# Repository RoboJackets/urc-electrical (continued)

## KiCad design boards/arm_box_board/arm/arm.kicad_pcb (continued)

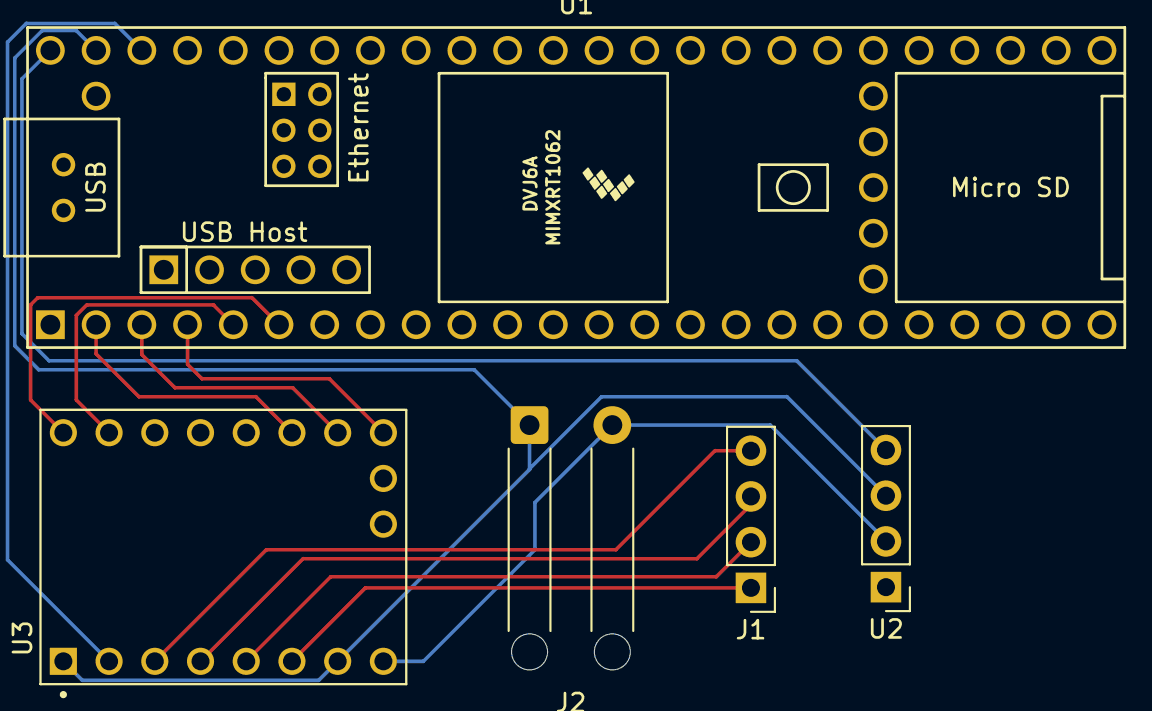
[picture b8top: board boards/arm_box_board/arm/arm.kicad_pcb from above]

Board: 2 copper layers, 5 parts (0 on the bottom side), 13 nets.

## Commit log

2024-03-07 Added BMS balance leads.
2024-04-11 Added Status Light Board
    To be merged into Main Board eventually
2024-04-11 arm_box_board
2024-04-13 Preliminary progress on science board.
2024-04-14 Finished preliminary routing. Used through-hole footprints.
2024-04-14 Updated board measurements.
2024-04-17 README.tex
2024-04-17 Rename README.tex to README.text
2024-04-17 Updated main schematic
2024-04-22 Updated Main PCB
2024-04-24 Added Ethernet module.
2024-04-24 Updated Arm board with ethernet
    updated on 04/24
2024-04-24 Added Logo
2024-04-24 Switched RX/TX pin position and IMU pin position
2024-04-25 moved science board to boards
2024-04-25 cap added
2024-04-25 Added logo to science board
2024-04-26 Added Holes to Main PCB
2024-04-28 Corrected Ethernet pin matches to teensy
2024-04-28 updated GND plane and unconnected pins
2024-04-28 updated science board-GND
2024-04-28 updated main board
2024-04-28 labelled digital input pins
2024-04-28 Extra pins/labels added
2024-04-28 last update
2024-05-02 Changes to Science and Arm Board
    Added pin labels to both boards
    Fixed Mislabeled Stepper Board Footprint in Arm board
    Added extra digital pins and ground in Science Board
2024-05-04 Removed I2C level converter from Science Board
    BRUH
    The temperature probe works running on 3.3V so the level converter for I2C wasn't even necessary on the Science Board. I have removed it from the schematic and updated the PCB layout.
2024-05-05 Prepared Boards for PCB Manufacture
    Added GND line for IMU on Main Board
    Fixed Silkscreen Text Size for PCB Manufacture on Science, Main, and Arm boards
    Generated Gerber Files for Science, Main, and Arm boards
2024-05-10 Changed Resistor Value for status light circuit in Main Board
    Updated value to 1k from 100 Ohms
2024-08-28 Solo Uno Module Side Panel PCB
    started
2024-09-15 Made Symbols and Footprint Library for RoboNav
2024-09-22 Add files via upload
    Updated Solo uno board
2024-10-14 Started 4 layer PCB
2024-11-03 4 layer main
2024-11-03 updated 4-layer
2024-11-03 4layer update
2024-11-04 Updated Solon
2024-11-11 Main 4layer with Gerber
2024-11-11 side panel with Gerber
    waiting for final aviation dimensions
2024-11-14 side panel
2024-11-14 Edited the GX-16-3 Footprint with correct dimensions
2024-11-17 updated solouno with new footprint
2024-11-18 Editing 4layer_main for Fabrication
    Made trace width 0.25mm
    Fixed power planes for 5v, 3.3v, and 24v
    Flipped around CAN transceiver pins
    Added RoboJackets font to board title
2024-11-21 updated Solouno
    Two pin for rocker switch
2024-11-21 solouno update
2024-12-05 Fixed MotorController Board PCB and Footprint for Aviation Connector
2025-03-07 Libraries added
2025-03-07 Closed the KiCAD window
2025-03-09 Restore stashed changes
2025-03-09 Revert changes
2025-03-09 Libraries readded
2025-04-18 Add files via upload
    Added schematics for new science PCB
2025-04-18 Create Science_Board_New
    Added Folder for New Science Board
2025-04-18 Created Folder for New Science Board
2025-04-18 Added New Science Board Schematics
2025-04-25 Create folder for New Science Board Gerber
2025-04-25 Added Gerber files for New Science Board
2025-04-29 Added New Arm PCB
2025-05-01 Added Gerber Files for arm board
2025-05-12 Arm_v2.0 & Science_v2.0 final version
